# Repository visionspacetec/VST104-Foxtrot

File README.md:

# VST104 Element Foxtrot - single MCU OBC for PC104
This repository contains the KiCad project and other documents created during the development of Element Foxtrot under [VST104 project](https://github.com/visionspacetec/VST104/). This FlatSat board is capable of hosting four PC104 format modules with LibreCube PC104 header pinout.

<p align="center">
  <br>
  
  <br><br>
  <b>Fig 1.</b> Element Foxtrot 3D visualisation.
  <br><br>
</p>

## Basic specifications
* **`modules:`** This flatsat board can accommodate up to four PC104 modules. The position and orientation of these slots are marked with silkscreen contours. Headers of the separate slots are connected in between each other concerning individual pins. Tracing of power lines is strengthened, and the ground is shared with the rest of the board.
* **`power circuitry:`** Upper part of the board carries power distribution circuitry. Power outputs of this part are connected to corresponding powerlines of PC104 slots. The usual setup is: **3.3[V], 5[V] and unregulated** - individually rated to deliver up to **5[A]** (depends on power source) to these power lines. Although different voltages in the regulated powerlines can be set by trimmers.
* **`power modes:`** A user can power this flatsat in two different modes. External power supply with standard **2[mm] JACK** or **USB-C** charger. A three-position slide switch *(on/off/on)* placed between these two connectors is used to select one or none of them. Both of the modes are rated for input voltage in range **7-14[V]** and input current up to **8[A]** for JACK mode and **6[A]** for USB-C mode.
* **`disconnection terminal:`** A set of removable jumpers is used to temporarily separate the power distribution circuitry from the rest of the flatsat. This is practical if a user needs to power the board from a different source or do not power it at all but is keen on not separating the power delivery circuitry by braking.
* **`4[mm] banana:`** After the disconnection terminal, just on the slots beginning, powerlines are placed a set of laboratory 2[mm] banana jacks. A user can use these jacks after disconnecting the corresponding terminals to point to any power or measuring device.

<p align="center">
  <br>
  
  <br><br>
  <b>Fig 1.</b> Graphical interpretation of segments described in "basic specifications" section.
  <br><br>
</p>

## Features

<p align="center">
  <br>
  
  <br><br>
  <b>Fig 1.</b> Graphical interpretation of segments described in "features" section.
  <br><br>
</p>

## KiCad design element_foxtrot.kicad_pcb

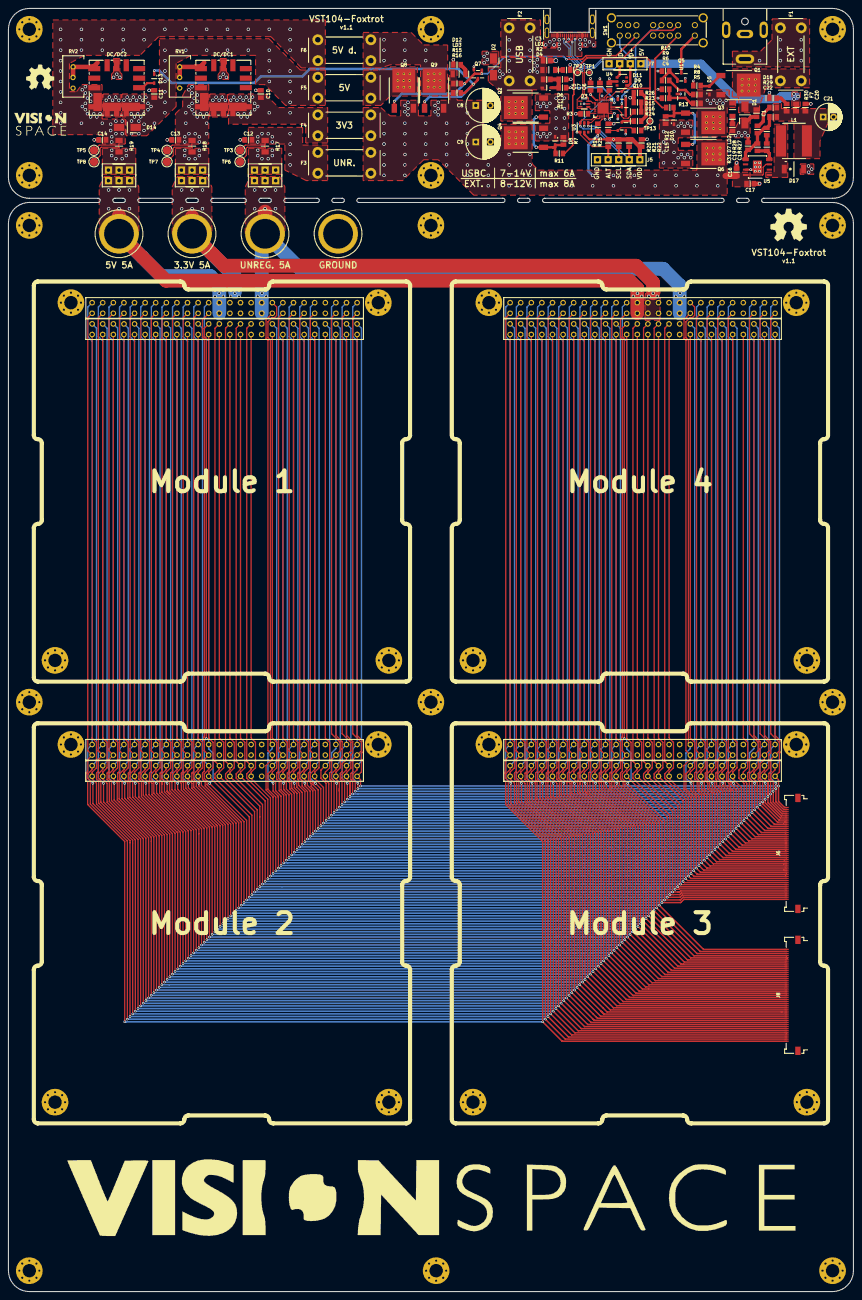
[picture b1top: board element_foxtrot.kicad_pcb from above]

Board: 4 copper layers, 202.5 x 307.5 mm, 143 parts (0 on the bottom side), 160 nets.

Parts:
C1: 100p; C_SMD_0805
C2, C5, C6, C7, C15: 1u; C_SMD_0805
C3: 4u7; C_SMD_0805
C4, C19: 1n; C_SMD_0805
C8, C9: 470u; CP_Radial_D8.0mm_P3.50mm_L11.5mm
C10, C11: 22u; C_SMD_0805
C12, C13, C14, C16, C20: 10u; C_SMD_0805
C17: 220n; C_SMD_0805
C18: 22n; C_SMD_0805
C21: 220u; CP_Radial_D6.3mm_P2.50mm_L11.2mm
C22: 2n2; C_SMD_0805
D1, D2: SMAJ15CA; D_SMA_DO-214AC_4.3x2.6mm
D3: ESDA25W5; SOT-323-5L_2.0x1.25mm
D4: BAT54JFILM; D_SOD-323_1.65x1.28mm
D5, D8, D10: DDZ15CSF; D_SOD-323-F_1.25x1.7mm
D6, D7: red; D_SMD_0805_LED
D9, D11: BAV199; SOT-23-3_2.9x1.3mm
D12, D18: green; D_SMD_0805_LED
D13: NSR0320MW2T1G; D_SOD-323_1.65x1.28mm
D14: FM4004W; D_SMA_DO-214AC_4.3x2.6mm
D15: yellow; D_SMD_0805_LED
D16: blue; D_SMD_0805_LED
D17: STPS3L60UFN; D_SMB-FN_DO-214AA-FN
DC/DC1, DC/DC2: Val**; OKL-T6-W12
F1, F2: 10A; FUSE_2AG_01110501Z
F3, F4, F5, F6: 5A; FUSE_2AG_01110501Z
F7: 2A1; C_SMD_0805
H1, H2, H3, H4, H5, H6, H7, H8, H9, H10, H11, H12, H13, H14, H15: MountingHole_Pad; MountingHole_3.2mm_M3_Pad_Via
J1: Ext_Power; PJ-063AH
J2, J3, J4: Val**; TSW-103-07-x-D
J5: Program; TSW-105-07-x-S
J6, J8: Conn_01x45; conn_FPC_45x0.5_505110-4591
J7: USB; TSW-104-07-x-S
L1: 22u; L_SMD_8040_8.0x8.0x4.2mm
LD1, LD2, LD3: AL5809; Power-DI-123_2.8x1.8x1mm
Module_1, Module_2, Module_3, Module_4: PC104_module; PC104_footprint
P1: Val**; CX90M-16P
Q1, Q2, Q3, Q4, Q6, Q8, Q9: SQD40061EL; TO-252AA_6.5x6.1mm
Q5, Q7, Q10: 2N7002BK; SOT-23-3_2.9x1.3mm
R1, R14, R27: 1k; R_SMD_0805
R2: 470; R_SMD_0805
R3, R7, R9, R10, R12, R15, R16, R24, R25: 100k; R_SMD_0805
R4, R20, R21, R22: 10k; R_SMD_0805
R5: 47k; R_SMD_0805
R6: 5k23; R_SMD_0805
R8: 20k; R_SMD_0805
R11, R13: 22k; R_SMD_0805
R17, R18, R19: 0; R_SMD_1206
R23, R30: 150; R_SMD_0805
R26, R28: 100; R_SMD_0805
R29: 5k1; R_SMD_0805
R31: 698; R_SMD_0805
RV1, RV2: 3k3; trimer_3296W_10.0x9.5x10.0
SW1: EG4319A; EG4319
TP1, TP2, TP13: TestPoint; scope_PAD_1mm
TP3, TP4, TP5, TP6, TP7, TP8: TestPoint_Alt; scope_PAD_2mm
TP9, TP10, TP11, TP12: TestPoint_Alt; KSE_PN6095
U1: TL432AIDBZR; SOT-23-3_2.9x1.3mm
U2: STUSB4500QTR; QFN-24_4.0x4.0mm_EP
U3, U4: USBLC6-4; SOT-23-6L_2.9x1.6mm
U5: L7985; HSOP8_3.9x4.9mm_EP

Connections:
+5V: F7.1, J7.1, R23.1, R26.1, U4.5
/ALTER: J5.4, R20.2, U2.19, U3.4
/CC1: D3.3, P1.A5, TP1.1, U2.1, U2.2
/CC2: D3.1, P1.B5, TP2.1, U2.4, U2.5
/GPIO: D15.1, U2.15
/H1-1: J8.4, Module_1.H1_1, Module_2.H1_1, Module_3.H1_1, Module_4.H1_1
/H1-2: J8.2, Module_1.H1_2, Module_2.H1_2, Module_3.H1_2, Module_4.H1_2
/H1-3: J8.8, Module_1.H1_3, Module_2.H1_3, Module_3.H1_3, Module_4.H1_3
/H1-4: J8.6, Module_1.H1_4, Module_2.H1_4, Module_3.H1_4, Module_4.H1_4
/H1-5: J8.12, Module_1.H1_5, Module_2.H1_5, Module_3.H1_5, Module_4.H1_5
/H1-6: J8.10, Module_1.H1_6, Module_2.H1_6, Module_3.H1_6, Module_4.H1_6
/H1-7: J8.16, Module_1.H1_7, Module_2.H1_7, Module_3.H1_7, Module_4.H1_7
/H1-8: J8.14, Module_1.H1_8, Module_2.H1_8, Module_3.H1_8, Module_4.H1_8
/H1-9: J8.20, Module_1.H1_9, Module_2.H1_9, Module_3.H1_9, Module_4.H1_9
/H1-10: J8.18, Module_1.H1_10, Module_2.H1_10, Module_3.H1_10, Module_4.H1_10
/H1-11: J8.24, Module_1.H1_11, Module_2.H1_11, Module_3.H1_11, Module_4.H1_11
/H1-12: J8.22, Module_1.H1_12, Module_2.H1_12, Module_3.H1_12, Module_4.H1_12
/H1-13: J8.28, Module_1.H1_13, Module_2.H1_13, Module_3.H1_13, Module_4.H1_13
/H1-14: J8.26, Module_1.H1_14, Module_2.H1_14, Module_3.H1_14, Module_4.H1_14
/H1-15: J8.32, Module_1.H1_15, Module_2.H1_15, Module_3.H1_15, Module_4.H1_15
/H1-16: J8.30, Module_1.H1_16, Module_2.H1_16, Module_3.H1_16, Module_4.H1_16
/H1-17: J8.36, Module_1.H1_17, Module_2.H1_17, Module_3.H1_17, Module_4.H1_17
/H1-18: J8.34, Module_1.H1_18, Module_2.H1_18, Module_3.H1_18, Module_4.H1_18
/H1-19: J8.40, Module_1.H1_19, Module_2.H1_19, Module_3.H1_19, Module_4.H1_19
/H1-20: J8.38, Module_1.H1_20, Module_2.H1_20, Module_3.H1_20, Module_4.H1_20
/H1-21: J8.44, Module_1.H1_21, Module_2.H1_21, Module_3.H1_21, Module_4.H1_21
/H1-22: J8.42, Module_1.H1_22, Module_2.H1_22, Module_3.H1_22, Module_4.H1_22
/H1-23: J6.3, Module_1.H1_23, Module_2.H1_23, Module_3.H1_23, Module_4.H1_23
/H1-24: J6.1, Module_1.H1_24, Module_2.H1_24, Module_3.H1_24, Module_4.H1_24
/H1-25: J6.5, Module_1.H1_25, Module_2.H1_25, Module_3.H1_25, Module_4.H1_25
/H1-26: J6.4, Module_1.H1_26, Module_2.H1_26, Module_3.H1_26, Module_4.H1_26
/H1-27: J6.7, Module_1.H1_27, Module_2.H1_27, Module_3.H1_27, Module_4.H1_27
/H1-28: J6.6, Module_1.H1_28, Module_2.H1_28, Module_3.H1_28, Module_4.H1_28
/H1-29: J6.9, Module_1.H1_29, Module_2.H1_29, Module_3.H1_29, Module_4.H1_29
/H1-30: J6.8, Module_1.H1_30, Module_2.H1_30, Module_3.H1_30, Module_4.H1_30
/H1-31: J6.11, Module_1.H1_31, Module_2.H1_31, Module_3.H1_31, Module_4.H1_31
/H1-32: J6.10, Module_1.H1_32, Module_2.H1_32, Module_3.H1_32, Module_4.H1_32
/H1-35: J6.15, Module_1.H1_35, Module_2.H1_35, Module_3.H1_35, Module_4.H1_35
/H1-36: J6.13, Module_1.H1_36, Module_2.H1_36, Module_3.H1_36, Module_4.H1_36
/H1-37: J6.19, Module_1.H1_37, Module_2.H1_37, Module_3.H1_37, Module_4.H1_37
/H1-38: J6.17, Module_1.H1_38, Module_2.H1_38, Module_3.H1_38, Module_4.H1_38
/H1-39: J6.23, Module_1.H1_39, Module_2.H1_39, Module_3.H1_39, Module_4.H1_39
/H1-40: J6.21, Module_1.H1_40, Module_2.H1_40, Module_3.H1_40, Module_4.H1_40
/H1-41: J6.27, Module_1.H1_41, Module_2.H1_41, Module_3.H1_41, Module_4.H1_41
/H1-42: J6.25, Module_1.H1_42, Module_2.H1_42, Module_3.H1_42, Module_4.H1_42
/H1-43: J6.31, Module_1.H1_43, Module_2.H1_43, Module_3.H1_43, Module_4.H1_43
/H1-44: J6.29, Module_1.H1_44, Module_2.H1_44, Module_3.H1_44, Module_4.H1_44
/H1-45: J6.33, Module_1.H1_45, Module_2.H1_45, Module_3.H1_45, Module_4.H1_45
/H1-46: J6.32, Module_1.H1_46, Module_2.H1_46, Module_3.H1_46, Module_4.H1_46
/H1-47: J6.37, Module_1.H1_47, Module_2.H1_47, Module_3.H1_47, Module_4.H1_47
/H1-48: J6.35, Module_1.H1_48, Module_2.H1_48, Module_3.H1_48, Module_4.H1_48
/H1-49: J6.41, Module_1.H1_49, Module_2.H1_49, Module_3.H1_49, Module_4.H1_49
/H1-50: J6.39, Module_1.H1_50, Module_2.H1_50, Module_3.H1_50, Module_4.H1_50
/H1-51: J6.45, Module_1.H1_51, Module_2.H1_51, Module_3.H1_51, Module_4.H1_51
/H1-52: J6.43, Module_1.H1_52, Module_2.H1_52, Module_3.H1_52, Module_4.H1_52
/H2-1: J8.1, Module_1.H2_1, Module_2.H2_1, Module_3.H2_1, Module_4.H2_1
/H2-2: J8.3, Module_1.H2_2, Module_2.H2_2, Module_3.H2_2, Module_4.H2_2
/H2-3: J8.5, Module_1.H2_3, Module_2.H2_3, Module_3.H2_3, Module_4.H2_3
/H2-4: J8.7, Module_1.H2_4, Module_2.H2_4, Module_3.H2_4, Module_4.H2_4
/H2-5: J8.9, Module_1.H2_5, Module_2.H2_5, Module_3.H2_5, Module_4.H2_5
/H2-6: J8.11, Module_1.H2_6, Module_2.H2_6, Module_3.H2_6, Module_4.H2_6
/H2-7: J8.13, Module_1.H2_7, Module_2.H2_7, Module_3.H2_7, Module_4.H2_7
/H2-8: J8.15, Module_1.H2_8, Module_2.H2_8, Module_3.H2_8, Module_4.H2_8
/H2-9: J8.17, Module_1.H2_9, Module_2.H2_9, Module_3.H2_9, Module_4.H2_9
/H2-10: J8.19, Module_1.H2_10, Module_2.H2_10, Module_3.H2_10, Module_4.H2_10
/H2-11: J8.21, Module_1.H2_11, Module_2.H2_11, Module_3.H2_11, Module_4.H2_11
/H2-12: J8.23, Module_1.H2_12, Module_2.H2_12, Module_3.H2_12, Module_4.H2_12
/H2-13: J8.25, Module_1.H2_13, Module_2.H2_13, Module_3.H2_13, Module_4.H2_13
/H2-14: J8.27, Module_1.H2_14, Module_2.H2_14, Module_3.H2_14, Module_4.H2_14
/H2-15: J8.29, Module_1.H2_15, Module_2.H2_15, Module_3.H2_15, Module_4.H2_15
/H2-16: J8.31, Module_1.H2_16, Module_2.H2_16, Module_3.H2_16, Module_4.H2_16
/H2-17: J8.33, Module_1.H2_17, Module_2.H2_17, Module_3.H2_17, Module_4.H2_17
/H2-18: J8.35, Module_1.H2_18, Module_2.H2_18, Module_3.H2_18, Module_4.H2_18
/H2-19: J8.37, Module_1.H2_19, Module_2.H2_19, Module_3.H2_19, Module_4.H2_19
/H2-20: J8.39, Module_1.H2_20, Module_2.H2_20, Module_3.H2_20, Module_4.H2_20
/H2-21: J8.41, Module_1.H2_21, Module_2.H2_21, Module_3.H2_21, Module_4.H2_21
/H2-22: J8.43, Module_1.H2_22, Module_2.H2_22, Module_3.H2_22, Module_4.H2_22
/H2-23: J8.45, Module_1.H2_23, Module_2.H2_23, Module_3.H2_23, Module_4.H2_23
/H2-24: J6.2, Module_1.H2_24, Module_2.H2_24, Module_3.H2_24, Module_4.H2_24
/H2-35: J6.12, Module_1.H2_35, Module_2.H2_35, Module_3.H2_35, Module_4.H2_35
/H2-36: J6.14, Module_1.H2_36, Module_2.H2_36, Module_3.H2_36, Module_4.H2_36
/H2-37: J6.16, Module_1.H2_37, Module_2.H2_37, Module_3.H2_37, Module_4.H2_37
/H2-38: J6.18, Module_1.H2_38, Module_2.H2_38, Module_3.H2_38, Module_4.H2_38
/H2-39: J6.20, Module_1.H2_39, Module_2.H2_39, Module_3.H2_39, Module_4.H2_39
/H2-40: J6.22, Module_1.H2_40, Module_2.H2_40, Module_3.H2_40, Module_4.H2_40
/H2-41: J6.24, Module_1.H2_41, Module_2.H2_41, Module_3.H2_41, Module_4.H2_41
/H2-42: J6.26, Module_1.H2_42, Module_2.H2_42, Module_3.H2_42, Module_4.H2_42
/H2-43: J6.28, Module_1.H2_43, Module_2.H2_43, Module_3.H2_43, Module_4.H2_43
/H2-44: J6.30, Module_1.H2_44, Module_2.H2_44, Module_3.H2_44, Module_4.H2_44
/H2-47: J6.34, Module_1.H2_47, Module_2.H2_47, Module_3.H2_47, Module_4.H2_47
/H2-48: J6.36, Module_1.H2_48, Module_2.H2_48, Module_3.H2_48, Module_4.H2_48
/H2-49: J6.38, Module_1.H2_49, Module_2.H2_49, Module_3.H2_49, Module_4.H2_49
/H2-50: J6.40, Module_1.H2_50, Module_2.H2_50, Module_3.H2_50, Module_4.H2_50
/H2-51: J6.42, Module_1.H2_51, Module_2.H2_51, Module_3.H2_51, Module_4.H2_51
/H2-52: J6.44, Module_1.H2_52, Module_2.H2_52, Module_3.H2_52, Module_4.H2_52
/PDO2: D11.3, R24.2, SW1.16, TP13.1, U2.20
/RST: R3.2, U2.6
/SCL: J5.3, R21.2, U2.7, U3.3
/SDA: J5.2, R22.2, U2.8, U3.1
/SUP_3V3: J3.2, J3.4, J3.6, Module_1.H2_27, Module_1.H2_28, Module_2.H2_27, Module_2.H2_28, Module_3.H2_27, Module_3.H2_28, Module_4.H2_27, Module_4.H2_28, TP11.1
/SUP_5V: J4.2, J4.4, J4.6, Module_1.H2_25, Module_1.H2_26, Module_2.H2_25, Module_2.H2_26, Module_3.H2_25, Module_3.H2_26, Module_4.H2_25, Module_4.H2_26, TP10.1
/SUP_BAT_1: Module_1.H2_45, Module_2.H2_45, Module_3.H2_45, Module_4.H2_45
/SUP_BAT_2: Module_1.H2_46, Module_2.H2_46, Module_3.H2_46, Module_4.H2_46
/SUP_UNREG: J2.2, J2.4, J2.6, Module_1.H2_33, Module_1.H2_34, Module_2.H2_33, Module_2.H2_34, Module_3.H2_33, Module_3.H2_34, Module_4.H2_33, Module_4.H2_34, TP9.1
/USB_N: J7.3, P1.A7, P1.B7, U4.1
/USB_P: J7.2, P1.A6, P1.B6, U4.4
/VOUT_3V3: C13.1, DC/DC1.4, DC/DC1.5, R18.2, TP4.1
/VOUT_5V: C14.1, D14.2, DC/DC2.4, DC/DC2.5, F6.1, R19.2, TP5.1
/VOUT_UNREG: C12.1, F3.1, R17.2, TP3.1
/VSINK: C8.1, C9.1, C16.1, C17.1, F3.2, F4.2, LD3.2, Q4.3, Q6.3, Q8.2, Q9.2, R14.2, R15.1, R16.1, U5.3, U5.8
GND: C1.1, C2.1, C3.1, C4.2, C5.1, C6.1, C7.1, C8.2, C9.2, C10.2, C11.2, C12.2, C13.2, C14.2, C15.2, C16.2, C17.2, C20.2, C21.2, D1.1, D2.1, D3.2, D6.1, D7.1, D9.1, D11.1, D12.1, D17.2, D18.1, DC/DC1.3, DC/DC1.7, DC/DC2.3, DC/DC2.7, J1.2, J1.MP, J5.5, J7.4, Module_1.H1_33, Module_1.H1_34, Module_1.H2_29, Module_1.H2_30, Module_1.H2_31, Module_1.H2_32, Module_2.H1_33, Module_2.H1_34, Module_2.H2_29, Module_2.H2_30, Module_2.H2_31, Module_2.H2_32, Module_3.H1_33, Module_3.H1_34, Module_3.H2_29, Module_3.H2_30, Module_3.H2_31, Module_3.H2_32, Module_4.H1_33, Module_4.H1_34, Module_4.H2_29, Module_4.H2_30, Module_4.H2_31, Module_4.H2_32, P1.A1, P1.A12, P1.B1, P1.B12, P1.MH, P1.MID, Q5.2, Q7.2, Q10.2, R3.1, R4.2, R6.2, R10.2, R25.2, R31.1, RV1.1, RV2.1, SW1.13, SW1.15, TP12.1, U1.3, U2.10, U2.12, U2.13, U2.25, U3.2, U4.2, U5.7, U5.25
unnamed: C1.2, D1.2, F1.1, Q1.3
unnamed: C2.2, D4.1, R1.1, R2.2
unnamed: C4.1, R5.2, R6.1, U1.1
unnamed: C5.2, D8.1, D9.2, D11.2, Q2.2, Q4.2, R7.1, U2.24
unnamed: C6.2, U2.21
unnamed: C7.2, U2.23
unnamed: C10.1, DC/DC1.2, F4.1
unnamed: C11.1, D14.1, DC/DC2.2, F5.1
unnamed: C18.1, C19.1, U5.4
unnamed: C18.2, R27.2
unnamed: C19.2, R27.1, R28.1, R29.1, R31.2, U5.5
unnamed: C20.1, C21.1, C22.1, F7.2, L1.2, R29.2, R30.1
unnamed: C22.2, R28.2
unnamed: D5.1, LD2.2, Q1.2, Q3.3, R5.1, R8.1
unnamed: D5.2, Q1.1, R4.1
unnamed: D6.2, LD1.1
unnamed: D7.2, LD2.1
unnamed: D8.2, Q2.1, Q4.1, R7.2, R11.1
unnamed: D9.3, SW1.4, U2.16
unnamed: D10.1, Q3.2, Q6.2, R12.1
unnamed: D10.2, Q3.1, Q6.1, R12.2, R13.1
unnamed: D12.2, LD3.1
unnamed: D13.1, Q7.3, Q9.1, R16.2
unnamed: D13.2, DC/DC2.1
unnamed: D15.2, R23.2
unnamed: D16.1, Q10.3
unnamed: D16.2, R26.2
unnamed: D17.1, L1.1, U5.1
unnamed: D18.2, R30.2
unnamed: DC/DC1.6, RV1.2, RV1.3
unnamed: DC/DC2.6, RV2.2, RV2.3
unnamed: F1.2, J1.1
unnamed: F2.2, P1.A4, P1.A9, P1.B4, P1.B9
unnamed: F5.2, Q8.3
unnamed: F6.2, Q9.3
unnamed: J2.1, J2.3, J2.5, R17.1, TP6.1
unnamed: J3.1, J3.3, J3.5, R18.1, TP7.1
unnamed: J4.1, J4.3, J4.5, R19.1, TP8.1
unnamed: Q5.1, R9.2, R10.1
unnamed: Q5.3, SW1.9
unnamed: Q7.1, Q8.1, R15.2, SW1.14
unnamed: Q10.1, R24.1, R25.1
unnamed: R1.2, U2.18
unnamed: R8.2, R9.1, U1.2
unnamed: R11.2, SW1.2
unnamed: R13.2, SW1.10
unnamed: R14.1, U2.9
VBUS: C3.2, D2.2, D4.2, F2.1, LD1.2, Q2.3, R2.1
VDD: C15.1, J5.1, R20.1, R21.1, R22.1, U2.22, U3.5

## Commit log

2020-11-19 Adds git submodule VST104 Libraries
2020-11-27 sync with library
